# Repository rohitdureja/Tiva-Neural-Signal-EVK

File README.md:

Tiva-Neural-Signal-EVK
======================

Evaluation Kit based on Texas Instruments Tiva ARM-Cortex-M4 MCU for wireless neural signal recording and analysis

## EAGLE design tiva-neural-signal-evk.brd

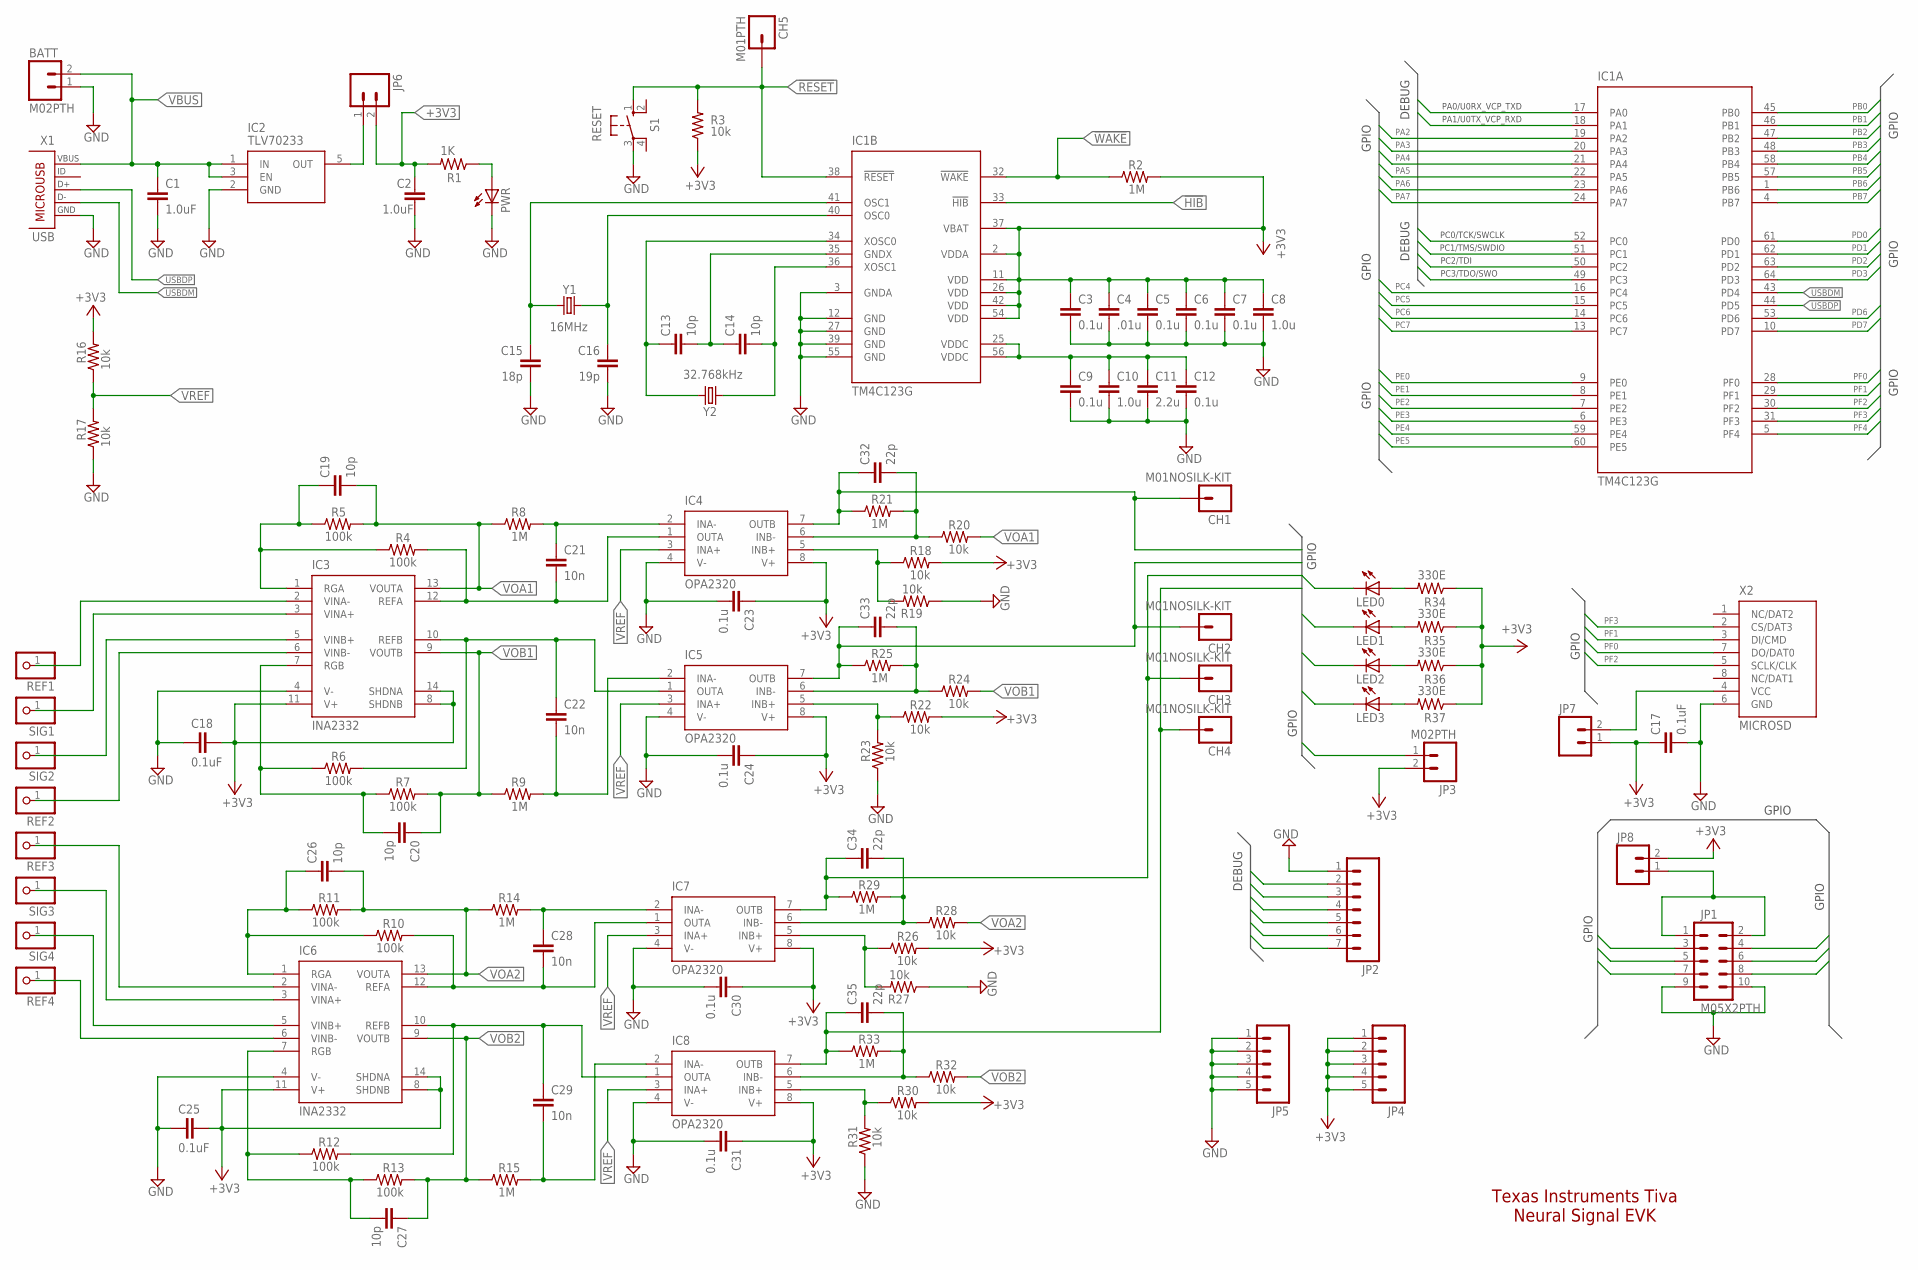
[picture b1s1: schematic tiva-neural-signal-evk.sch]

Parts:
BATT: M02PTH; 1X02
C1, C2: 1.0uF; C0603
C3, C5, C6, C7, C9, C12, C23, C24, C30, C31: 0.1u; C0603
C4: .01u; C0603
C8, C10: 1.0u; C0603
C11: 2.2u; C0603
C13, C14, C19, C20, C26, C27: 10p; C0603
C15: 18p; C0603
C16: 19p; C0603
C17, C18, C25: 0.1uF; C0603
C21, C22, C28, C29: 10n; C0603
C32, C33, C34, C35: 22p; C0603
CH1, CH2, CH3, CH4: M01NOSILK-KIT; 1X01NS-KIT
CH5: M01PTH; 1X01
IC1: TM4C123G; LQFP64
IC2: TLV70233; SOT23-5
IC3, IC6: INA2332; TSSOP14
IC4, IC5, IC7, IC8: OPA2320; MSOP08
JP1: M05X2PTH; AVR_ICSP
JP2: M07; 1X07
JP3: M02PTH; 1X02
JP4, JP5: M05PTH; 1X05
JP6, JP7, JP8: M021X02_NO_SILK; 1X02_NO_SILK
LED0, LED1, LED2, LED3: LEDCHIP-LED0603; CHIP-LED0603
PWR: LEDCHIP-LED0603; CHIP-LED0603
R1: 1K; R0603
R2, R8, R9, R14, R15, R21, R25, R29, R33: 1M; R0603
R3, R16, R17, R18, R19, R20, R22, R23, R24, R26, R27, R28, R30, R31, R32: 10k; R0603
R4, R5, R6, R7, R10, R11, R12, R13: 100k; R0603
R34, R35, R36, R37: 330E; R0603
REF1, REF2, REF3, REF4: PINHD-1X1; 1X01
S1: RESET; B3F-10XX
SIG1, SIG2, SIG3, SIG4: PINHD-1X1; 1X01
X1: USB; USB-MICROB
X2: MICROSD; PUSH-PUSH
Y1: 16MHz; CRYSTAL-SMD-5X3
Y2: 32.768kHz; CRYSTAL-32KHZ-SMD

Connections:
!HIB!: IC1.33 (!HIB!)
!RESET!: CH5.1, IC1.38 (!RESET!), R3.2, S1.1 (S)
!WAKE!: IC1.32 (!WAKE!), R2.1
+3V3: C2.1, C3.1, C4.1, C5.1, C6.1, C7.1, C8.1, C17.1, C18.1, C23.1, C24.1, C25.1, C30.1, C31.1, IC1.2 (VDDA), IC1.11 (VDD), IC1.26 (VDD), IC1.37 (VBAT), IC1.42 (VDD), IC1.54 (VDD), IC3.8 (SHDNB), IC3.11 (V+), IC3.14 (SHDNA), IC4.8 (V+), IC5.8 (V+), IC6.8 (SHDNB), IC6.11 (V+), IC6.14 (SHDNA), IC7.8 (V+), IC8.8 (V+), JP3.2, JP4.1, JP4.2, JP4.3, JP4.4, JP4.5, JP6.2, JP7.1, JP8.2, R1.2, R2.2, R3.1, R16.2, R18.2, R22.2, R26.2, R30.2, R34.1, R35.1, R36.1, R37.1
GND: BATT.1, C1.2, C2.2, C3.2, C4.2, C5.2, C6.2, C7.2, C8.2, C9.2, C10.2, C11.2, C12.2, C15.2, C16.2, C17.2, C18.2, C23.2, C24.2, C25.2, C30.2, C31.2, IC1.3 (GNDA), IC1.12 (GND), IC1.27 (GND), IC1.39 (GND), IC1.55 (GND), IC2.2 (GND), IC3.4 (V-), IC4.4 (V-), IC5.4 (V-), IC6.4 (V-), IC7.4 (V-), IC8.4 (V-), JP1.9, JP1.10, JP2.1, JP5.1, JP5.2, JP5.3, JP5.4, JP5.5, PWR.C, R17.1, R19.1, R23.1, R27.1, R31.1, S1.3, X1.GND, X2.6 (GND)
unnamed: C20.2, IC3.7 (RGB), R6.1, R7.1
unnamed: C22.1, IC3.10 (REFB), IC5.1 (OUTA), R6.2
unnamed: C26.1, IC6.1 (RGA), R10.1, R11.1
unnamed: C19.1, IC3.1 (RGA), R4.1, R5.1
unnamed: C21.2, IC3.12 (REFA), IC4.1 (OUTA), R4.2
unnamed: C14.2, IC1.36 (XOSC1), Y2.X1 (1)
unnamed: C13.2, C14.1, IC1.35 (GNDX)
unnamed: C13.1, IC1.34 (XOSC0), Y2.X2 (2)
unnamed: C16.1, IC1.40 (OSC0), Y1.3 (2)
unnamed: C15.1, IC1.41 (OSC1), Y1.1
unnamed: PWR.A, R1.1
unnamed: C28.2, IC6.12 (REFA), IC7.1 (OUTA), R10.2
unnamed: C27.2, IC6.7 (RGB), R12.1, R13.1
unnamed: C21.1, IC4.2 (INA-), R8.2
unnamed: C22.2, IC5.2 (INA-), R9.2
unnamed: C29.1, IC6.10 (REFB), IC8.1 (OUTA), R12.2
unnamed: C28.1, IC7.2 (INA-), R14.2
unnamed: C29.2, IC8.2 (INA-), R15.2
unnamed: IC4.5 (INB+), R18.1, R19.2
unnamed: C32.2, IC4.6 (INB-), R20.1, R21.2
unnamed: IC3.2 (VINA-), REF1.1
unnamed: IC7.5 (INB+), R26.1, R27.2
unnamed: IC5.5 (INB+), R22.1, R23.2
unnamed: C33.2, IC5.6 (INB-), R24.1, R25.2
unnamed: IC3.3 (VINA+), SIG1.1
unnamed: C34.2, IC7.6 (INB-), R28.1, R29.2
unnamed: IC6.6 (VINB-), REF4.1
unnamed: IC8.5 (INB+), R30.1, R31.2
unnamed: C35.2, IC8.6 (INB-), R32.1, R33.2
unnamed: IC6.5 (VINB+), SIG4.1
unnamed: LED0.A, R34.2
unnamed: IC3.6 (VINB-), REF2.1
unnamed: IC6.2 (VINA-), REF3.1
unnamed: IC6.3 (VINA+), SIG3.1
unnamed: LED1.A, R35.2
unnamed: LED2.A, R36.2
unnamed: LED3.A, R37.2
unnamed: IC2.5 (OUT), JP6.1
unnamed: JP7.2, X2.4 (VCC)
unnamed: JP1.1, JP1.2, JP8.1
PA0: IC1.17 (PA0), JP2.2
PA1: IC1.18 (PA1), JP2.3
PA2: IC1.19 (PA2)
PA3: IC1.20 (PA3)
PA4: IC1.21 (PA4)
PA5: IC1.22 (PA5)
PA6: IC1.23 (PA6)
PA7: IC1.24 (PA7)
PB0: IC1.45 (PB0), LED0.C
PB1: IC1.46 (PB1), LED1.C
PB2: IC1.47 (PB2), LED2.C
PB3: IC1.48 (PB3), LED3.C
PB4: IC1.58 (PB4)
PB5: IC1.57 (PB5)
PB6: IC1.1 (PB6), JP1.3
PB7: IC1.4 (PB7), JP1.8
PC0: IC1.52 (PC0), JP2.4
PC1: IC1.51 (PC1), JP2.5
PC2: IC1.50 (PC2), JP2.6
PC3: IC1.49 (PC3), JP2.7
PC4: IC1.16 (PC4)
PC5: IC1.15 (PC5)
PC6: IC1.14 (PC6)
PC7: IC1.13 (PC7)
PD0: IC1.61 (PD0), JP1.5
PD1: IC1.62 (PD1), JP1.4
PD2: IC1.63 (PD2), JP1.7
PD3: IC1.64 (PD3), JP1.6
PD6: IC1.53 (PD6)
PD7: IC1.10 (PD7)
PE0: C35.1, CH4.1, IC1.9 (PE0), IC8.7 (OUTB), R33.1
PE1: C34.1, CH3.1, IC1.8 (PE1), IC7.7 (OUTB), R29.1
PE2: C33.1, CH2.1, IC1.7 (PE2), IC5.7 (OUTB), R25.1
PE3: C32.1, CH1.1, IC1.6 (PE3), IC4.7 (OUTB), R21.1
PE4: IC1.59 (PE4)
PE5: IC1.60 (PE5)
PF0: IC1.28 (PF0), X2.7 (DO/DAT0)
PF1: IC1.29 (PF1), X2.3 (DI/CMD)
PF2: IC1.30 (PF2), X2.5 (SCLK/CLK)
PF3: IC1.31 (PF3), JP3.1, X2.2 (CS/DAT3)
PF4: IC1.5 (PF4)
SIG2: IC3.5 (VINB+), SIG2.1
USBDM: IC1.43 (PD4), X1.D-
USBDP: IC1.44 (PD5), X1.D+
VBUS: BATT.2, C1.1, IC2.1 (IN), IC2.3 (EN), X1.VBUS
VDDC: C9.1, C10.1, C11.1, C12.1, IC1.25 (VDDC), IC1.56 (VDDC)
VOA1: C19.2, IC3.13 (VOUTA), R5.2, R8.1, R20.2
VOA2: C26.2, IC6.13 (VOUTA), R11.2, R14.1, R28.2
VOB1: C20.1, IC3.9 (VOUTB), R7.2, R9.1, R24.2
VOB2: C27.1, IC6.9 (VOUTB), R13.2, R15.1, R32.2
VREF: IC4.3 (INA+), IC5.3 (INA+), IC7.3 (INA+), IC8.3 (INA+), R16.1, R17.2

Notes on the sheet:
Texas Instruments Tiva Neural Signal EVK
GPIO
DEBUG
PA0/U0RX_VCP_TXD
PA1/U0TX_VCP_RXD
PC0/TCK/SWCLK
PC1/TMS/SWDIO
PC2/TDI
PC3/TDO/SWO

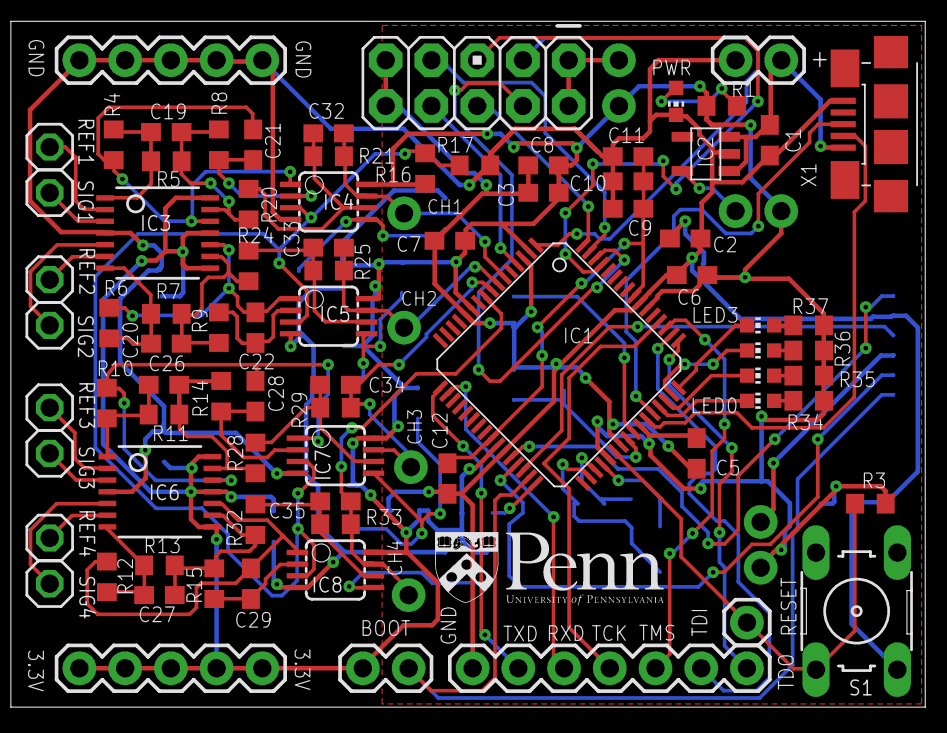
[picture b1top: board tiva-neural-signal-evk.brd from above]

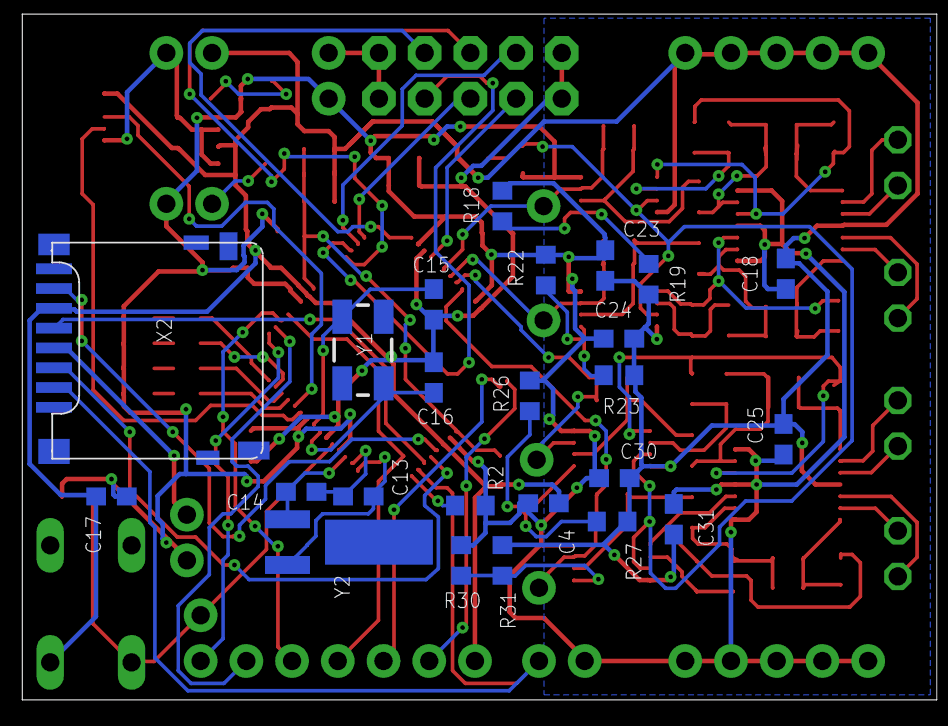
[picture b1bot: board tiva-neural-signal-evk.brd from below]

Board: 2 copper layers, 113 parts (24 on the bottom side), 78 nets.

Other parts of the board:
U$1: PENNLOGO

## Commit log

2014-06-10 created initial repository
2014-06-10 added power supply
2014-06-10 deleted unnecessary backup files
2014-06-10 added MCU power circuit
2014-06-11 completed mcu control
2014-06-11 added mcu gpio and debug buses
2014-06-11 added mcu pin names and debug
2014-06-12 added SD card in SPI mode
2014-06-12 added 2-ch instrumentation amp w/ op-amp gain stage
2014-06-12 added another 2-ch instrumentation amplifer
2014-06-16 completed amplifier stage design
2014-06-17 laid out components
2014-06-17 placed components and defined net classes
2014-06-17 added usb and adc connections
2014-06-18 added everything. initial routing complete with signal planes
2014-06-19 Revert "added everything. initial routing complete with signal planes"
    This reverts commit afc261f9183dc80193b5e18bad7752eddb98d99b.
2014-06-19 Revert "Revert "added everything. initial routing complete with signal planes""
    This reverts commit d55bffc2993c446258426b3721d1dfd936908fa6.
2014-06-19 added reset for debug
2014-06-20 tnames, bnames fixed. manually routed.
2014-06-20 fixed component names
2014-06-23 final board sent for fab
2014-06-23 final board sent for fab. updated 3d files
2014-07-03 minor edit
2014-07-29 added component values
2014-07-29 latest commit

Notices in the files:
parts and their libraries:
SparkFun-FreqCtrl: Licensing: Creative Commons ShareAlike 4.0 International - https://creativecommons.org/licenses/by-sa/4.0
